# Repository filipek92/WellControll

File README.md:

View this project on [CADLAB.io](https://cadlab.io/project/1268). 

# WellControll

Board for controlling of well (measuring water level, flow, temperature) over RS485 or USB using ATmega32U4.

Firmware is based on [HardwareSerialRS485 by Michael Jonker](https://github.com/MichaelJonker/HardwareSerialRS485) as multi-master low layer access to shared medium with colision detection.

This board should be integrated into home RS485 network, proxy service to MQTT system is planned for usage of hi level logic service (HomeAssistant....).

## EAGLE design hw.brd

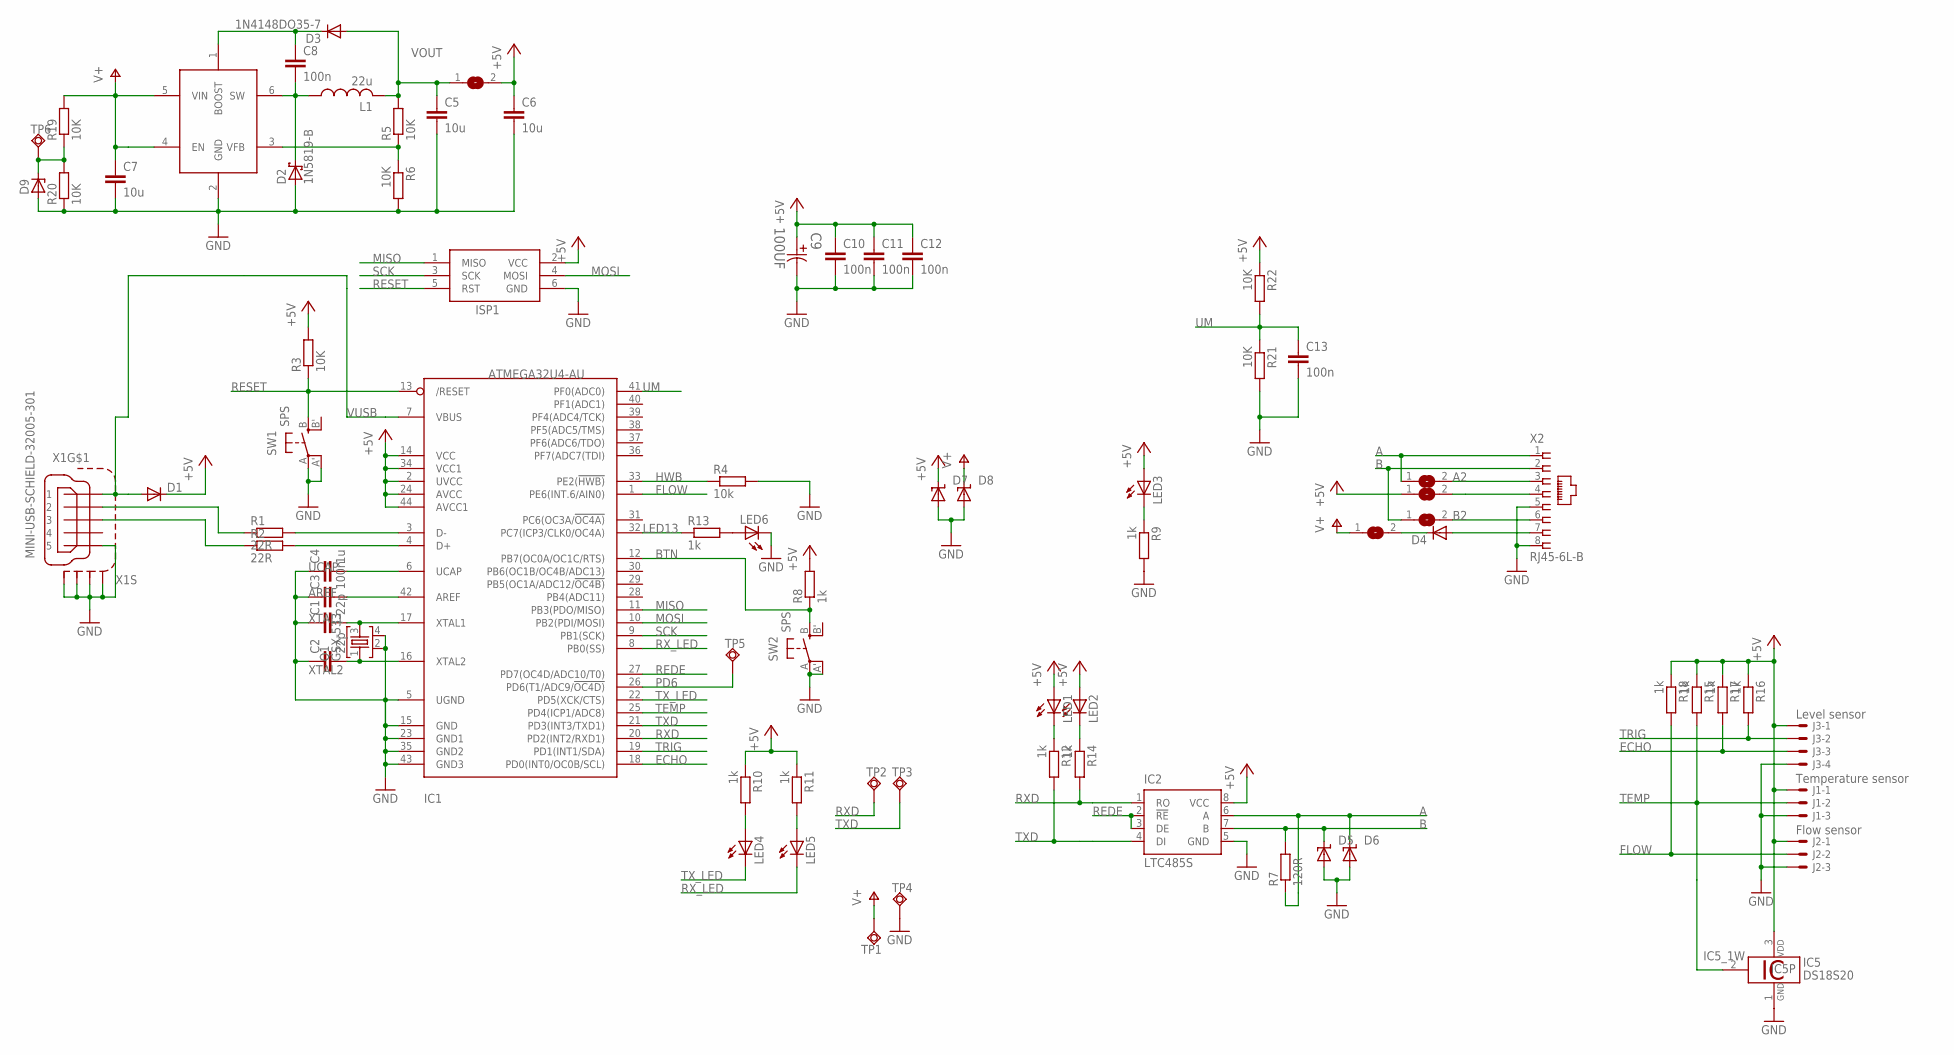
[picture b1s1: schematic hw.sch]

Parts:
C1, C2: 22p; C0805K
C3, C8, C10, C11, C12, C13: 100n; C0805K
C4: 1u; C0805K
C5, C6, C7: 10u; C0805K
C9: 100UF; CAPAE660X610N
D1: DIODE-MICROMELF-W; MICROMELF-W
D2: 1N5819-B; DO41-7.6
D3: 1N4148DO35-7; DO35-7
D4: DIODE-MINIMELF; MINIMELF
D5, D6, D7, D8: SUPPRESSOR-SMBG; SMBG
D9: ZENER-DIODESMB; SMB
IC1: ATMEGA32U4-AU; TQFP44
IC2: LTC485S; SOIC8
IC3: MCP16301/H; SOT23-6
IC5: DS18S20; TO92-
ISP1: AVRISP-6; AVRISP
J1: Temperature sensor; 6410-03
J2: Flow sensor; 6410-03
J3: Level sensor; 6410-04
L1: 22u; 0207/12
LED1, LED2, LED3, LED4, LED5, LED6: LEDCHIPLED_0805; CHIPLED_0805
Q1: GSX-533; 5032
R1, R2: 22R; M0805
R3, R5, R6, R19, R20, R21, R22: 10K; M0805
R4: 10k; M0805
R7: 120R; M0805
R8, R9, R10, R11, R12, R13, R14, R15, R16, R17, R18: 1k; M0805
SJ1, SJ2, SJ3, SJ4, SJ5: SJ
SW1, SW2: SPS; EVQ-Q2
TP1, TP2, TP3, TP4, TP5, TP6: TPSQTP20SQ; TP20SQ
X1: MINI-USB-SCHIELD-32005-301; 32005-301
X2: RJ45-6L-B; RJ45-NO-SHIELD

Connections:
5V_IN: SJ4.2, X2.4
24V_IN: D4.A, X2.7
+5V: C6.1, C9.1, C10.1, C11.1, C12.1, D1.C, D7.C, IC1.2 (UVCC), IC1.14 (VCC), IC1.24 (AVCC), IC1.34 (VCC1), IC1.44 (AVCC1), IC2.8 (VCC), IC5.3 (VDD), ISP1.2 (VCC), J1.1, J2.1, J3.1, LED1.A, LED2.A, LED3.A, R3.2, R8.2, R10.1, R11.1, R15.1, R16.1, R17.1, R18.1, R22.1, SJ4.1, SJ5.2
A: D6.C, IC2.6 (A), R7.1, SJ1.1, X2.1
A2: SJ1.2, X2.3
AREF: C3.2, IC1.42 (AREF)
B: D5.C, IC2.7 (B), R7.2, SJ2.1, X2.2
B2: SJ2.2, X2.6
BOOST: C8.1, D3.C, IC3.1 (BOOST)
BTN: IC1.12 (PB7(OC0A/OC1C/RTS)), R8.1, SW2.B (S)
D+: IC1.4 (D+), R2.2
D-: IC1.3 (D-), R1.2
ECHO: IC1.18 (PD0(INT0/OC0B/SCL)), J3.3, R17.2
FB: IC3.3 (VFB), R5.1, R6.1
FLOW: IC1.1 (PE6(INT.6/AIN0)), J2.2, R18.2
GND: C1.1, C2.1, C3.1, C4.1, C5.2, C6.2, C7.2, C9.2, C10.2, C11.2, C12.2, C13.2, D2.A, D5.A, D6.A, D7.A, D8.A, D9.A, IC1.5 (UGND), IC1.15 (GND), IC1.23 (GND1), IC1.35 (GND2), IC1.43 (GND3), IC2.5 (GND), IC3.2 (GND), IC5.1 (GND), ISP1.6 (GND), J1.3, J2.3, J3.4, LED6.C, Q1.2 (GND1), Q1.4 (GND2), R4.2, R6.2, R9.2, R20.1, R21.2, SW1.A, SW1.A' (P1), SW2.A, SW2.A' (P1), TP4.TP, X1.5, X1.M1 (S1), X1.M2 (S2), X1.M3 (S3), X1.M4 (S4), X2.5, X2.8
HWB: IC1.33 (PE2(!HWB)), R4.1
LED13: IC1.32 (PC7(ICP3/CLK0/OC4A)), R13.1
MISO: IC1.11 (PB3(PDO/MISO)), ISP1.1 (MISO)
MOSI: IC1.10 (PB2(PDI/MOSI)), ISP1.4 (MOSI)
unnamed: LED4.A, R10.2
unnamed: LED5.A, R11.2
unnamed: D4.C, SJ3.2
unnamed: LED1.C, R12.1
unnamed: LED2.C, R14.1
unnamed: LED3.C, R9.1
unnamed: LED6.A, R13.2
unnamed: D9.C, R19.1, R20.2, TP6.TP
PD6: IC1.26 (PD6(T1/ADC9/!OC4D)), TP5.TP
REDE: IC1.27 (PD7(OC4D/ADC10/T0)), IC2.2 (!RE), IC2.3 (DE)
RESET: IC1.13 (/RESET), ISP1.5 (RST), R3.1, SW1.B (S)
RXD: IC1.20 (PD2(INT2/RXD1)), IC2.1 (RO), R14.2, TP2.TP
RX_LED: IC1.8 (PB0(SS)), LED5.C
SCK: IC1.9 (PB1(SCK)), ISP1.3 (SCK)
SW: C8.2, D2.C, IC3.6 (SW), L1.1
TEMP: IC1.25 (PD4(ICP1/ADC8)), IC5.2 (1W), J1.2, R15.2
TRIG: IC1.19 (PD1(INT1/SDA)), J3.2, R16.2
TXD: IC1.21 (PD3(INT3/TXD1)), IC2.4 (DI), R12.2, TP3.TP
TX_LED: IC1.22 (PD5(XCK/CTS)), LED4.C
UCAP: C4.2, IC1.6 (UCAP)
UM: C13.1, IC1.41 (PF0(ADC0)), R21.1, R22.2
USB+: R2.1, X1.3
USB-: R1.1, X1.2
V+: C7.1, D8.C, IC3.4 (EN), IC3.5 (VIN), R19.2, SJ3.1, TP1.TP
VOUT: C5.1, D3.A, L1.2, R5.2, SJ5.1
VUSB: D1.A, IC1.7 (VBUS), X1.1
XTAL1: C1.2, IC1.17 (XTAL1), Q1.3 (XTAL2)
XTAL2: C2.2, IC1.16 (XTAL2), Q1.1 (XTAL1)

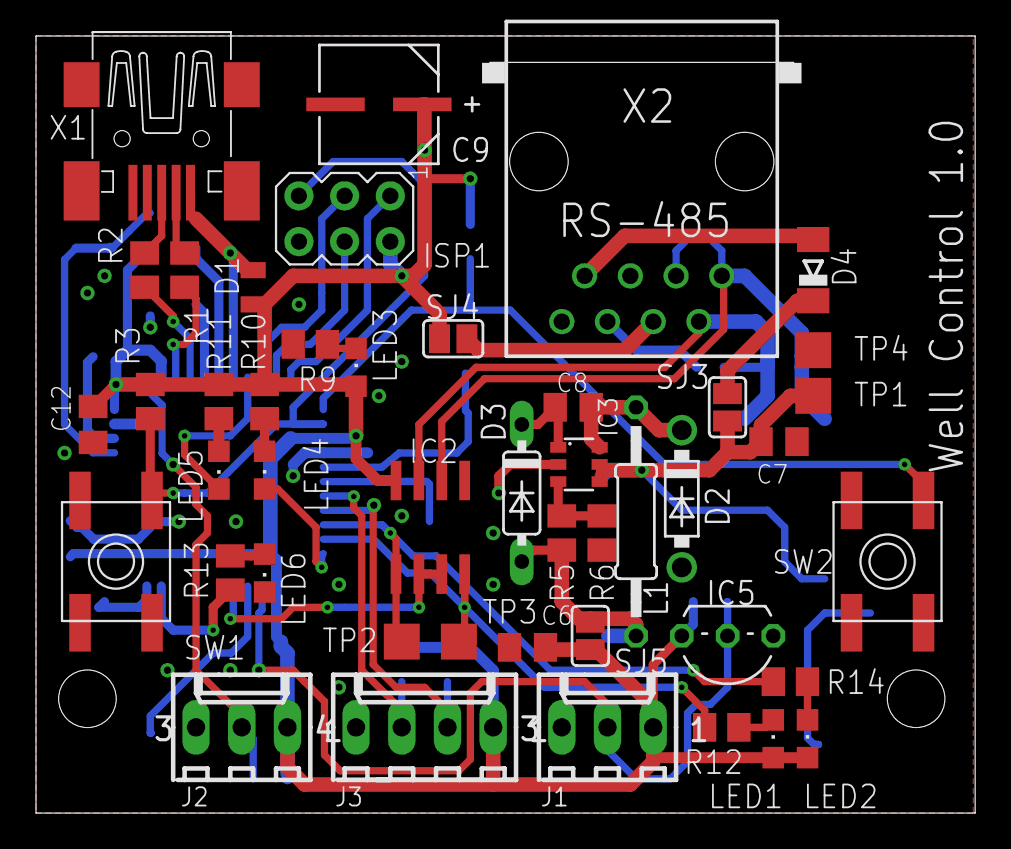
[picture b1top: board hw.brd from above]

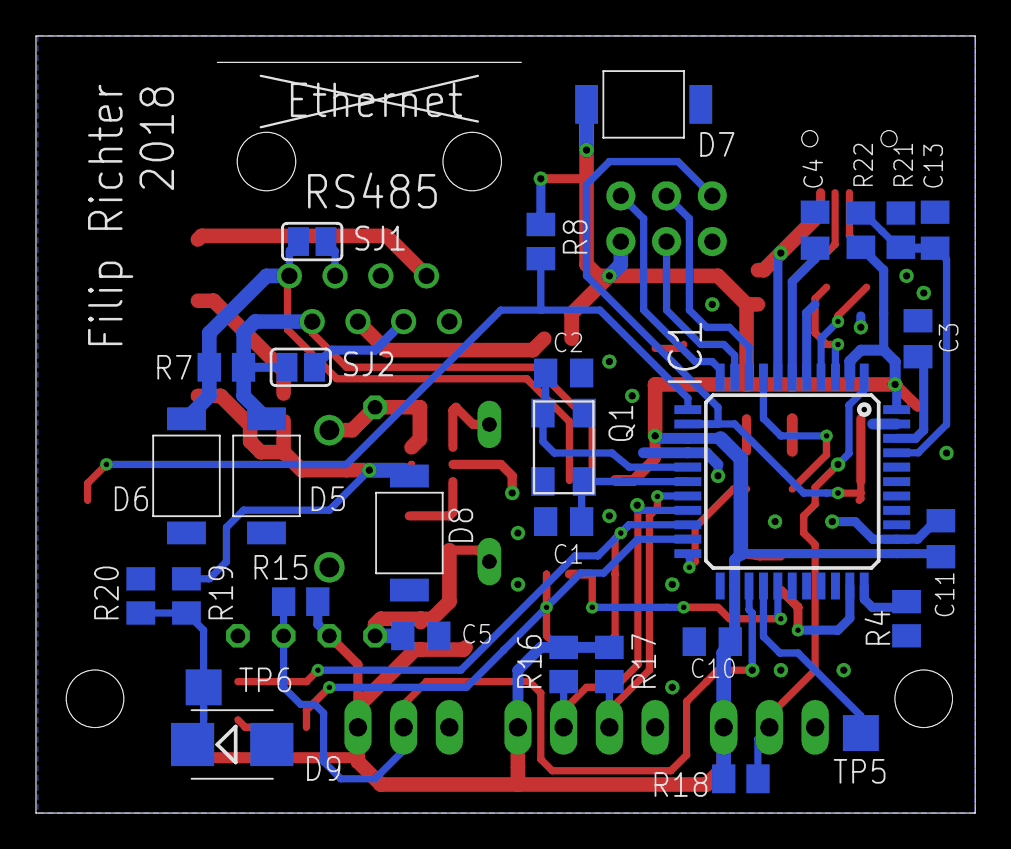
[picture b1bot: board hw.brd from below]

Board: 2 copper layers, 52.2 x 43.2 mm, 75 parts (30 on the bottom side), 48 nets.

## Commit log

2018-08-27 First version kickout
2018-08-27 Backlink to CADLAB.io has been added.
2018-08-27 Set layers visibility
2018-08-28 Changed library of crystal
2018-09-06 Minor fixes
2018-09-06 Added firmware
2018-09-06 Files structure changed
